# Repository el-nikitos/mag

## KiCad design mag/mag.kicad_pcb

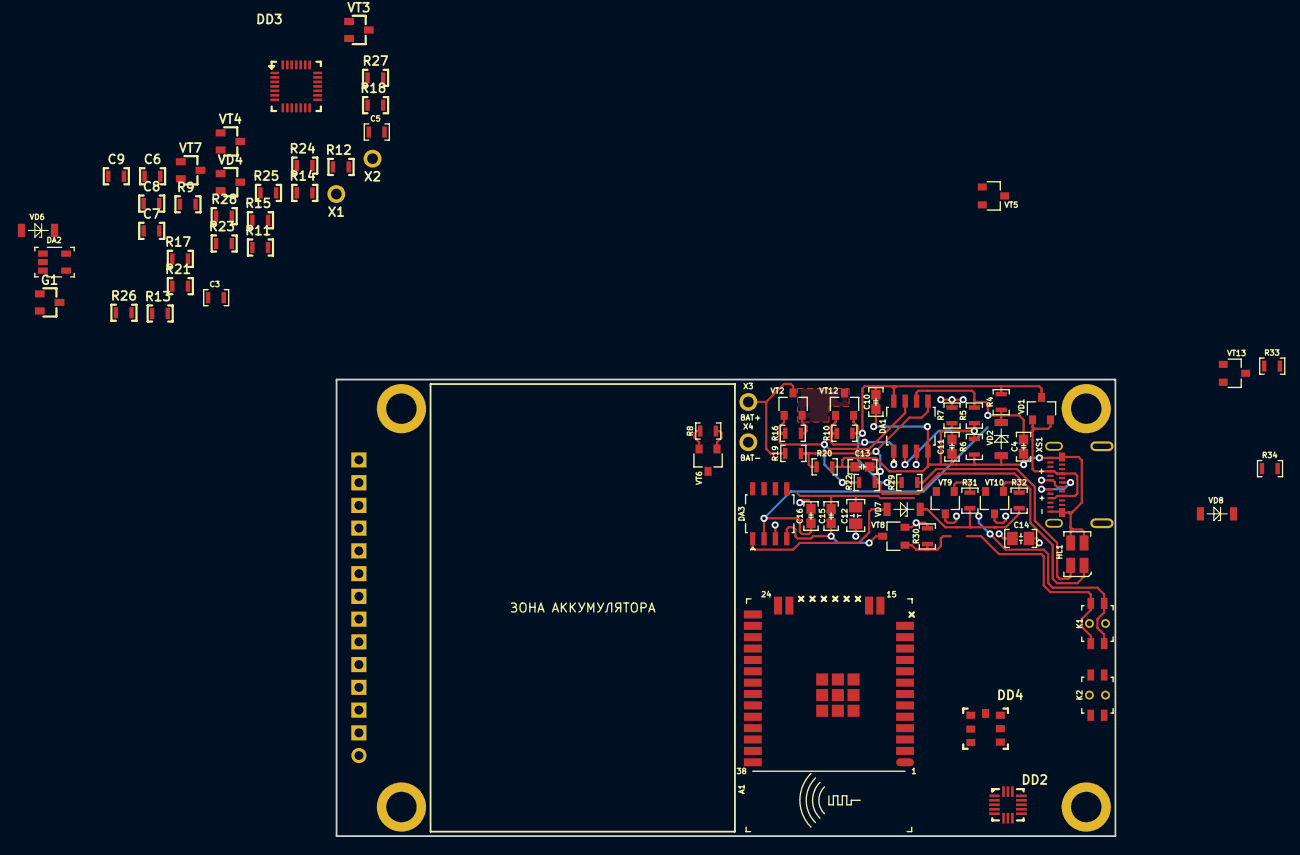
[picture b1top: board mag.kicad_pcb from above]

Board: 4 copper layers, 87.0 x 51.0 mm, 80 parts (1 on the bottom side), 55 nets.

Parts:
A1: модуль_esp32_wroom_32_SMD_noSD; ESP32_WROOM32_pnp_noSD
C3, C5: Конденсатор_керамический; Конденсатор_SMD_0603_pnp
C4, C10, C11, C13, C15, C16: Конденсатор*0,1мкФ*25В*0603; Конденсатор_SMD_IEC_0603
C6, C7, C8, C9: Конденсатор_керамический; Конденсатор_SMD_0603
C12, C14: Конденсатор*10мкФ*16В*0805; Конденсатор_SMD_IEC_0805
D1: LOGO; ni_10x10
DA1, DA3: ОУ_LM358DT; SO-8
DA2: ОУ_LMV321ILT; SOT-23-5_pnp
DD2: LIS3DH; акселерометр_LIS3DH
DD3: Преобразователь_CP2102(USB-UART); Микросхема_CP2102
DD4: Датчик_bmp180; BMP180
G1: ИОП_LM4040BIM3-2.5_NOPB; Транзистор_IRLML6344TR_SOT-23
HL1: Светодиод_сдвоенный_KPB-3025SURKCGKC; Светодиод_SMD_m3025
HL2: TFT-дисплей_ST7735_ILI9341; TFT_2.8_INCH
K1, K2: Кнопка_KLS7-TS5401-1.35-250-T; Кнопка_KLS7-TS5401
R4, R6, R8, R10, R22, R29, R31, R32, R34: Резистор*1кОм*0603; Резистор_SMD_0603_0,065_Вт_pnp
R5, R16, R30, R33: Резистор*10кОм*0603; Резистор_SMD_0603_0,065_Вт_pnp
R7: Резистор*1Ом*0603; Резистор_SMD_0603_0,065_Вт_pnp
R9, R11, R12, R13, R14, R15, R17, R18, R21, R23, R24, R25: Резистор_0,065Вт; Резистор_SMD_0603_0,065_Вт
R19: Резистор*7,5кОм*0603; Резистор_SMD_0603_0,065_Вт_pnp
R20: Резистор*11кОм*0603; Резистор_SMD_0603_0,065_Вт_pnp
R26, R27, R28: Резистор_0,065Вт; Конденсатор_SMD_0603
VD1: Набор_диодов_2Д803АС9; Корпус_КТ-46
VD2, VD7, VD8: Стабилитрон*2,4В*SOD80; SOD-80
VD4: Диоды_шоттки_BAR43CFILM; Транзистор_IRLML6344TR_SOT-23
VD6: Стабилитрон_BZV55-C3V9; SOD-80
VT2, VT6, VT12: Транзистор_полевой_P-канал(IRLML2246TRPBF); Корпус_КТ-46
VT3, VT7: Транзистор_полевой_P-канал(IRLML2246TRPBF); Транзистор_IRLML6344TR_SOT-23
VT4: Транзистор_полевой_N-IRLML6344TR; Транзистор_IRLML6344TR_SOT-23
VT5: Транзистор*npn*0,5А*45В*SOT23; Корпус_КТ-46
VT8, VT13: Транзистор_полевой_N-канальный_КП526А9; Корпус_КТ-46
VT9, VT10: Транзистор*pnp*0,5А*45В*SOT23; Корпус_КТ-46
X1, X2, X3, X4: отверстие_под_пайку; ОтверстиеD1.2
XS1: UBS-type-C-105450-0101&упрощенная; usb-type-c

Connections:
3V3: A1.2, C5.1, C14.1, DA3.3, HL2.1, R11.2, R24.1, VD6.2, VT7.3, VT9.3, VT10.3
5V: C10.1, DA1.8, R4.1, R10.1, R29.2, VD1.3, VT12.2
/3V: C8.1, C9.1, DD2.1, DD2.7, DD2.8, DD2.14, DD4.2, DD4.3
/AN.2V5.REF: A1.8, DA2.3, G1.1, R21.2
/AN.BAT.MEASURE: A1.7, R17.2, R18.1
/BAT-REF-2V4: R34.2, VD8.2
/BAT.LOAD: C3.1, DA2.5, R17.1, R21.1, R23.1, VT3.3, VT7.2
/BOOT: A1.25, K2.1, K2.2
/BUTT-TURN: K1.1, K1.2, R30.2, VT8.1
/CUR-DIRECT: DA1.1, R10.2, VT12.1
/D+: XS1.A6, XS1.B6
/D-: XS1.A7, XS1.B7
/DIRECT: R8.2, VT6.1, VT8.3, VT13.3
/ESP-TURN: R33.2, VT13.1
/EXT.BUTT: R15.2, VD4.3, X2.1
/GND-IN: C4.2, C10.2, C11.2, C13.2, DA1.4, HL1.2, HL1.4, R6.2, R7.2, R20.2, VD2.1, XS1.A1, XS1.A12, XS1.B1, XS1.B12
/I2C_SCL: DD2.4, DD4.5
/I2C_SDA: DD2.6, DD4.6
/LDO-DIRECT: DA3.1, VD7.1
/MISO: A1.31, HL2.9
/MOSI: A1.37, HL2.6
/REF-0V22: C11.1, DA1.2, R5.2, R6.1
/REF-2V4: C4.1, DA1.6, R4.2, R5.1, VD2.2
/REF-3V3: C16.1, DA3.2
/RESET: A1.3, R9.2
/SCK: A1.30, HL2.7
/TFT-CS: A1.29, HL2.3
/TFT-DC: A1.26, HL2.5
/TFT-LED: A1.13, HL2.8
/TFT-RES: A1.23, HL2.4
/U.FB: DA2.1, R24.2, R25.1
/UIN: VD1.1, VD1.2, XS1.A4, XS1.A9, XS1.B4, XS1.B9
/USB_pwr: C6.1, DD3.7, DD3.8, R27.1
/USB_pwr_gnd: C6.2, C7.2, C8.2, C9.2, DD2.5, DD2.12, DD3.3, DD4.7, R26.2, R28.1
/VBAT: C15.1, DA3.8, R34.1, VT6.3
/VOL-DIRECT: DA1.7, R16.2, R22.2, VT2.1
/VOL-SENS: C13.1, DA1.5, R19.2, R20.1
/max0.22A: R16.1, VT2.2, VT12.3
/max4V: C12.1, K1.3, K1.4, R8.1, R19.1, VT2.3, VT6.2, X3.1
GND: A1.1, A1.15, A1.38, A1.39, C3.2, C5.2, C12.2, C14.2, C16.2, DA1.3, DA2.2, DA3.4, G1.2, HL2.2, K2.3, K2.4, R7.1, R13.2, R18.2, R25.2, R30.1, R33.1, VD6.1, VD8.1, VT4.2, VT8.2, VT13.2, X1.1, X4.1
unnamed: C7.1, DD3.6
unnamed: DA2.4, R23.2, VT7.1
unnamed: DD2.10, R26.1
unnamed: DD3.9, R27.2
unnamed: DD3.11, R28.2
unnamed: HL1.1, R22.1
unnamed: HL1.3, R29.1
unnamed: R9.1, R11.1
unnamed: R12.1, VT3.2
unnamed: R12.2, VD4.1, VD4.2, VT3.1, VT4.3
unnamed: R13.1, R14.2, VT4.1
unnamed: R31.1, VT9.1
unnamed: R31.2, R32.2, VD7.2
unnamed: R32.1, VT10.1
unnamed: VT9.2, VT10.2

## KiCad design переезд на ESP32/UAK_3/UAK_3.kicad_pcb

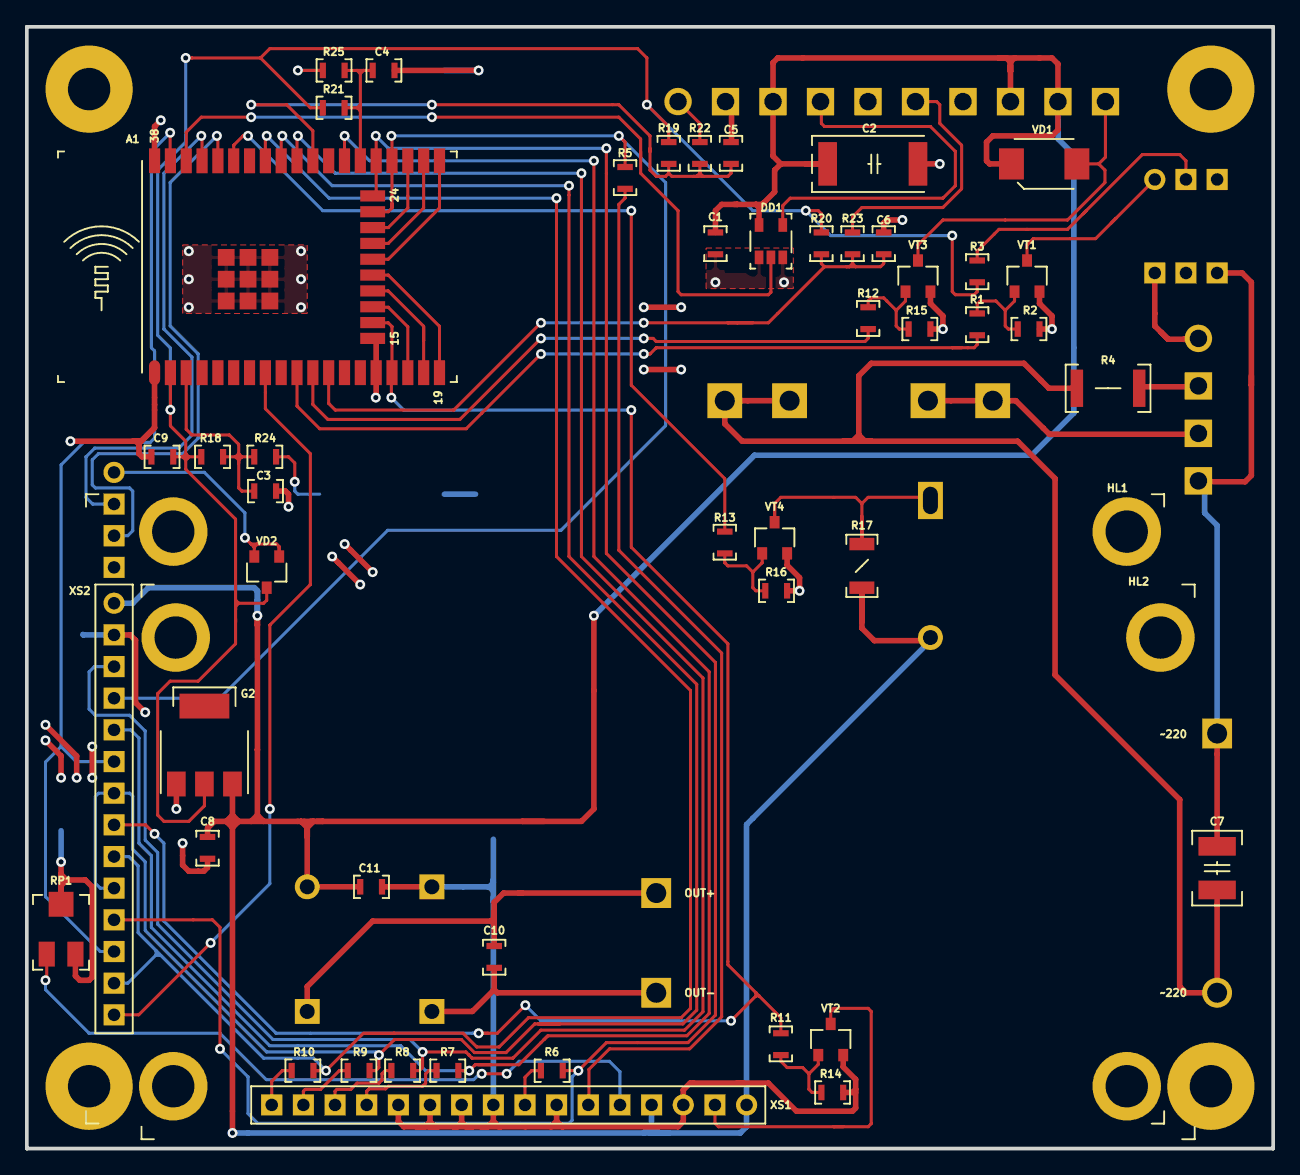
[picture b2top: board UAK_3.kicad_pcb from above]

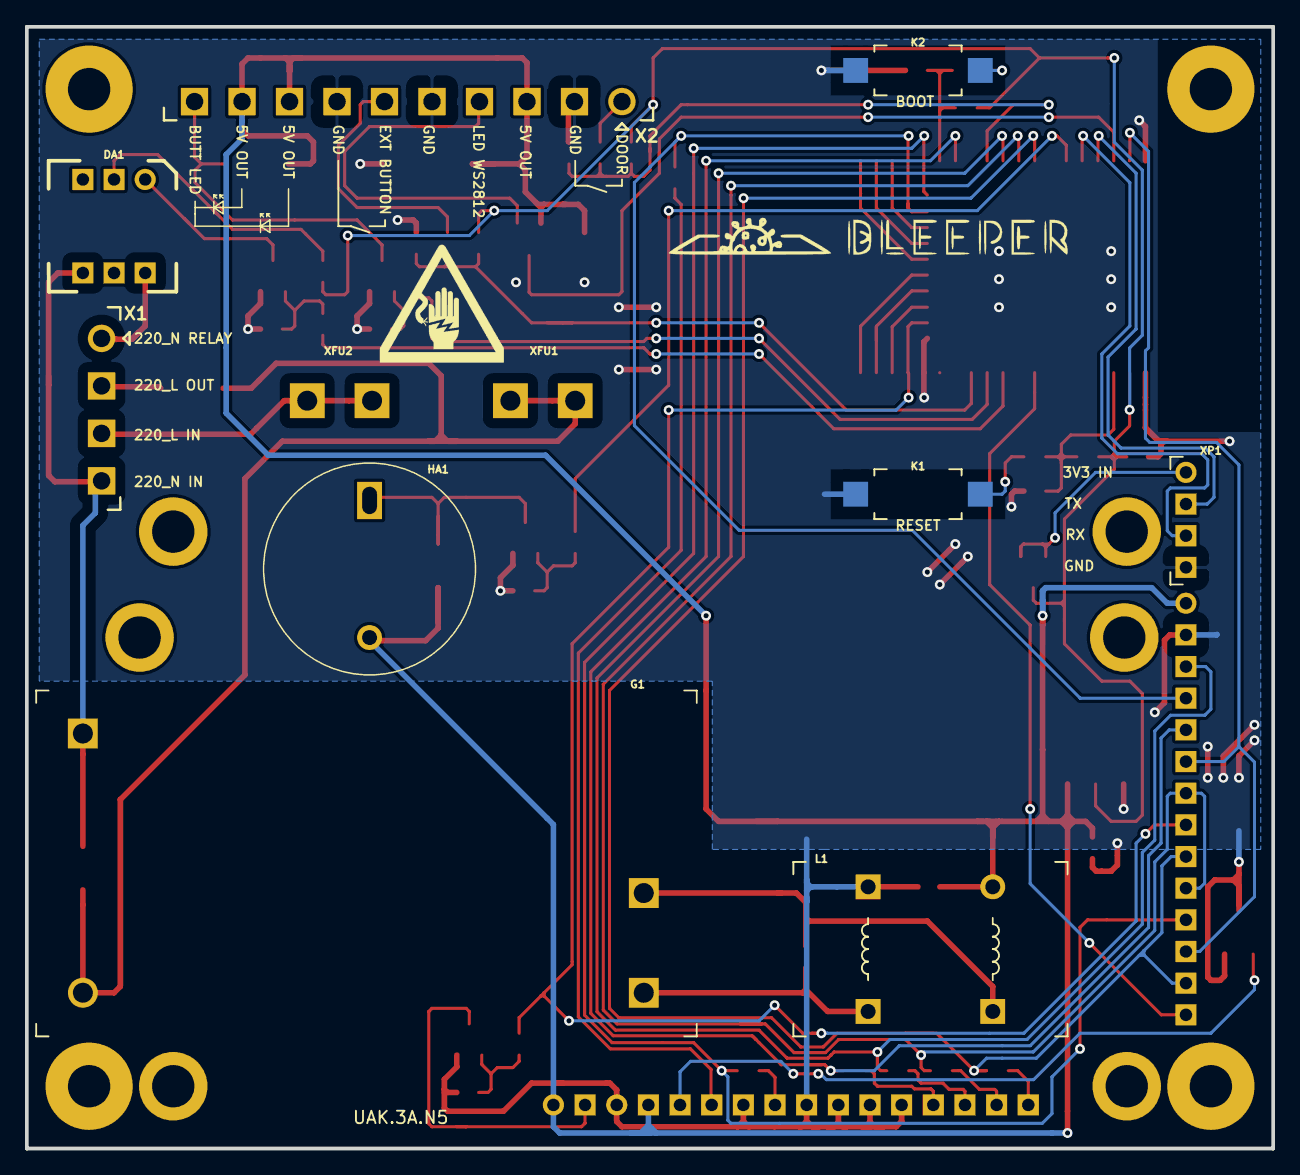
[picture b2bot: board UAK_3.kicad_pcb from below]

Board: 2 copper layers, 100.0 x 90.0 mm, 65 parts (13 on the bottom side), 51 nets.

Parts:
A1: модуль_esp32_wrover_OR_wroom32_SMD; ESP32_WROVER_or_WROOM32_pnp
C1, C3, C4, C5, C6, C8, C9, C10, C11: Конденсатор_керамический; Конденсатор_SMD_0603_pnp
C2: Конденсатор_К53-56А-32В-22_мкФ+-10проц.; Конденсатор_тантал_SMD_m7343_pnp
C7: Конденсатор_керамический; Конденсатор_SMD_1210_pnp
D1: LOGO; danger_220
D2: LOGO; bleeper_4x33
DA1: МОП-реле_КР293КП1Б; DIP6
DD1: Повторитель_M74VHC1GT125; SOT-23-5_pnp
G1: AC-DC-преобразователь_IRM-15-5; AC-DC_IRM-20-12
G2: стабилизатор_нерегулируемый_LM1117GS-3.3; Транзистор_NPN_SOT223_pnp
HA1: Излучатель_HPA17F; Зуммер_HPA17F
HL1: TFT-дисплей_ST7735_ILI9341; TFT_2.8_INCH
HL2: Жидкокристалический_индикатор_MT-16S2H-2KLW; ЖК_MT-16S2H_2DRL
K1, K2: Кнопка_FSMSM
L1: Дроссель_B82731-T2132-A20_2х6.8мГн_1.3А_250В; Дроссель_B82731
R1, R2, R3, R5, R6, R7, R8, R9, R10, R11, R12, R13, R14, R15, R16, R18, R19, R20, R21, R22, R23, R24, R25: Резистор_0,065Вт; Резистор_SMD_0603_0,065_Вт_pnp
R4: Резистор_0,5Вт; Резистор_SMD_2010-0,5_Вт_pnp
R17: Резистор_0,25Вт; Резистор_SMD_1206-0,25_Вт_pnp
RP1: Резистор_подстроечный_PVA3A103; резистор_подстроечный_3314J-1_pnp
VD1: Диод_шоттки_SK16; Диод_SMB_pnp
VD2: Набор_диодов_BAR43CFILM; Корпус_КТ-46_pnp
VT1, VT2, VT3, VT4: Транзистор_полевой_N-канальный_IRLML6344TR; Корпус_КТ-46_pnp
X1: Клеммник_х4; Клеммник_х4_шаг3,81_15EDGRC
X2: Клеммник_х10; Клеммник_х10_шаг3,81_15EDGRC
X3, X4, X5, X6: Крепежное_отверстие_М3; Крепежное_Отверстие_под_М3
XFU1, XFU2: Держатель_предохранителя_KLS5-266; Держатель_5х20
XP1: Вилка_WF-4R; Вилка_СНП389-4ВП32-1-1

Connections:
/3V3: A1.2, C9.1, G2.2, R3.2, R18.1, R19.1, R20.1, R21.1, VD2.3
/5V: C1.1, C2.1, C8.1, C11.1, DD1.5, G2.3, HA1.1, HL1.1, HL2.2, HL2.15, L1.1, R17.1, VD1.1, X2.3, X2.8, X2.9
/220_L: X1.3, XFU2.1
/220_L_FU: C7.1, G1.L, R4.1, XFU1.1
/220_L_OUT: R4.2, X1.2
/220_N: C7.2, DA1.4, G1.N, X1.4
/220_N_OUT: DA1.6, X1.1
/BOOT_SEL: A1.25, C4.1, R21.2, R25.2
/BOOT_UART_RX: A1.34, XP1.3
/BOOT_UART_TX: A1.35, XP1.2
/BUTT_1: R23.1, X2.6
/BUZZER: A1.33, R13.2
/DOOR_1: R22.1, X2.1
/DOOR_SENSOR: A1.28, C5.2, R19.2, R22.2
/D_OUT_1: VD1.2, VT3.3, X2.10
/EN_RESET: A1.3, C3.1, R18.2, R24.2
/EXT_BUTTON: A1.12, C6.2, R20.2, R23.2
/GND: A1.1, A1.15, A1.38, A1.39, C1.2, C2.2, C3.2, C4.2, C5.1, C6.1, C8.2, C9.2, C11.2, DD1.1, DD1.3, G2.1, HL1.2, HL2.1, HL2.5, HL2.7, HL2.8, HL2.9, HL2.10, K1.1, K2.1, L1.3, R2.2, R14.2, R15.2, R16.2, RP1.2, RP1.3, VT1.2, VT2.2, VT3.2, VT4.2, X2.2, X2.5, X2.7, XP1.4
/LCD_A0: A1.23, HL1.4, R5.2
/LCD_DATA_4: A1.26, HL1.5, R7.2
/LCD_DATA_5: A1.29, HL1.3, R8.2
/LCD_DATA_6: A1.30, HL1.7, HL1.10, R9.2
/LCD_DATA_7: A1.31, HL1.9, HL1.13, R10.2
/LCD_E: A1.24, HL1.11, R6.2
/LCD_LED: A1.16, HL1.8, R11.2
/LED_OUT: DD1.4, X2.4
/LED_WS2812: A1.36, DD1.2
/MC_220_OUT: A1.10, R1.2
/MC_OUT_1: A1.11, R12.2
/MOSI: A1.37, HL1.6, HL1.12
/SUPPLY_POWER/5V_NOISE: C10.1, G1.+V, L1.6
/TOUCH_IRQ: A1.8, HL1.14
unnamed: C10.2, G1.-V, L1.4
unnamed: DA1.1, VT1.3
unnamed: DA1.2, R3.1
unnamed: HA1.2, R17.2, VT4.3
unnamed: HL2.3, RP1.1
unnamed: HL2.4, R5.1
unnamed: HL2.6, R6.1
unnamed: HL2.11, R7.1
unnamed: HL2.12, R8.1
unnamed: HL2.13, R9.1
unnamed: HL2.14, R10.1
unnamed: HL2.16, VT2.3
unnamed: K1.2, R24.1
unnamed: K2.2, R25.1
unnamed: R1.1, R2.1, VT1.1
unnamed: R11.1, R14.1, VT2.1
unnamed: R12.1, R15.1, VT3.1
unnamed: R13.1, R16.1, VT4.1
unnamed: VD2.1, VD2.2, XP1.1

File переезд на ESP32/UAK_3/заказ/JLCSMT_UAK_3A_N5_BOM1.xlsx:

Comment | Designator | Footprint | LCSC Part #（optional） |  | new name
ESP32-WROOM-32E | A1 | SMD38,18x25.5 | C701341 | 0 | ESP32-WROOM-32E
100nF 50V | C1 | 0603_C | C14663 | 0 | 100nF 50V
100uF 10V | C2 | CASE-D_7343 | C110548 | 0 | 100uF 10V
100nF 50V | C3 | 0603_C | C14663 | 0 | 100nF 50V
100nF 50V | C4 | 0603_C | C14663 | 1 | ?
100nF 50V | C5 | 0603_C | C14663 | 1 | ?
100nF 50V | C6 | 0603_C | C14663 | 1 | ?
22nF 1kV | C7 | 1210_C | C304015 | 0 | 22nF 1kV
10uF 10V | C8 | 0603_C | C19702 | 0 | 10uF 10V
10uF 10V | C9 | 0603_C | C19702 | 1 | ?
10uF 10V | C10 | 0603_C | C19702 | 1 | ?
10uF 10V | C11 | 0603_C | C19702 | 1 | ?
M74VHC1GT125DT1G | DD1 | SOT-23-5 | C23654 | 0 | M74VHC1GT125DT1G
SC1117-3.3V | G2 | SOT-223 | C173386 | 0 | SC1117-3.3V
240Ω | R1 | 0603_R | C23350 | 0 | 240Ω
10kΩ | R2 | 0603_R | C25804 | 0 | 10kΩ
150Ω | R3 | 0603_R | C22808 | 0 | 150Ω
130Ω | R4 | 2010_R | C25459 | 0 | 130Ω
240Ω | R5 | 0603_R | C23350 | 0 | 240Ω
240Ω | R6 | 0603_R | C23350 | 1 | ?
240Ω | R7 | 0603_R | C23350 | 1 | ?
240Ω | R8 | 0603_R | C23350 | 1 | ?
240Ω | R9 | 0603_R | C23350 | 1 | ?
240Ω | R10 | 0603_R | C23350 | 1 | ?
240Ω | R11 | 0603_R | C23350 | 1 | ?
240Ω | R12 | 0603_R | C23350 | 1 | ?
240Ω | R13 | 0603_R | C23350 | 1 | ?
10kΩ | R14 | 0603_R | C25804 | 0 | 10kΩ
10kΩ | R15 | 0603_R | C25804 | 1 | ?
10kΩ | R16 | 0603_R | C25804 | 1 | ?
1kΩ | R17 | 1206_R | C4410 | 0 | 1kΩ
10kΩ | R18 | 0603_R | C25804 | 0 | 10kΩ
10kΩ | R19 | 0603_R | C25804 | 1 | ?
10kΩ | R20 | 0603_R | C25804 | 1 | ?
10kΩ | R21 | 0603_R | C25804 | 1 | ?
240Ω | R22 | 0603_R | C23350 | 0 | 240Ω
240Ω | R23 | 0603_R | C23350 | 1 | ?
240Ω | R24 | 0603_R | C23350 | 1 | ?
240Ω | R25 | 0603_R | C23350 | 1 | ?
50K Variable Resistors | RP1 | 3314J | C50895 | 0 | 50K Variable Resistors
MDD SS24B | VD1 | SMB(DO-214AA) | C78395 | 0 | MDD SS24B
BAT54CLT1G | VD2 | SOT-23-3 | C68978 | 0 | BAT54CLT1G
IRLML6344TR | VT1 | SOT-23-3 | C8545 | 0 | IRLML6344TR
IRLML6344TR | VT2 | SOT-23-3 | C8545 | 1 | ?
IRLML6344TR | VT3 | SOT-23-3 | C8545 | 1 | ?
IRLML6344TR | VT4 | SOT-23-3 | C8545 | 1 | ?

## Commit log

2019-04-07 проект связи с альтиметром
2019-05-21 начата схема для макета альтиметра
2019-05-25 есть схема макета, начал распологать элементы
2019-05-31 есть топология и габарит, не расставлен обвес
2019-05-31 трассировка завершена, требуется маркировка
2019-06-02 закончена трассировка и маркировка
    не подготавливались файлы производства
2019-06-06 добавлены файлы производства
2019-06-29 готово отображение на lcd
2019-07-14 в тестовое ПО добавлен высотомер и вывод на дисплей
2019-07-14 добавлена библиотека, требуется перепайка проца на 328
2019-09-08 подготавливается переделка под стационарные датчики
2019-09-08 экспериментальные данные
2019-09-25 выложена схема питания и преобразователя
2019-09-26 на схеме не отражены внешняя i2c-eeprom
2019-09-27 закончена около-боевая разводка, на плате оставлены штыревые разъемы
2019-10-19 сформированны файлы для заказа
2019-10-24 добавлен перечень ПКИ
2019-10-27 добавлены данные полного заряда аккумулятора
    полный заряд от 3 до 4,3 В - 3 часа, принято заряда - 295 мА*ч (84 %)
2019-11-10 тестовая прошивка, замечания по плате
    тестовая прошивка - обмен по usb-uart
    замечания по плате - добавлены пометки для изсправления в следующих версиях
2019-11-10 arduino test: adc test
2019-11-16 инициализирован проект в Atmel Studio
2019-11-17 библиотека bmp180, замечания к схеме
2019-11-17 проверка исправности LCD дисплея
    обнаружена проблема с питанием контроллера: p-канальный транзистор через что-то утекает и сам открывается
2019-11-18 выключение после 10 циклов проверки
2019-11-19 при выводе на дисплей 6, 8 или 9 резко повышается ток
2019-11-19 проверена работа кнопок
    требуется переделать схему под дополнительный транзистор
2019-11-24 оптимизирована функция вывода на дисплей, setup перенесен в atmel studio
2019-11-24 записана карта регистров калибровки bmp180
2019-11-30 определена температура, выведена на экран
2019-11-30 excel с формулами для проверки расчетов
2019-12-01 обновлена excel для проверки барометра
2019-12-01 добавлена функция оцифровки и пред. обработки барометра
2019-12-01 удалены распаковынные библиотеки ардуино по bmp180
2019-12-01 доопределен адрес дисплея, добавлена функция инициализации дисплея
2019-12-07 добавлены логитипы, есть функция вывода логотипа на oled при старте
2019-12-15 правки прошивки, добавление таблицы данных давления (расчет)
2021-02-21 исправления в i2c-scaner
2023-02-26 инициирован переезд на ESP32
2023-03-04 подготовлена схема заряда АБ, начата схема питания МК
2023-03-05 подготовлена схема включения 3,3В, не установлен источник 2,5В
2023-03-05 вынесен, но не подключен LDO на 2,5В
2023-03-12 схема включения 2.5В по кнопке
2023-03-19 инициирована замена транзисторов pnp на p-канальные
